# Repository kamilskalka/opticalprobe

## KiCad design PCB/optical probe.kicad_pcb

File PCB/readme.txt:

This folder contains the KiCad project and gerber files of the PCB

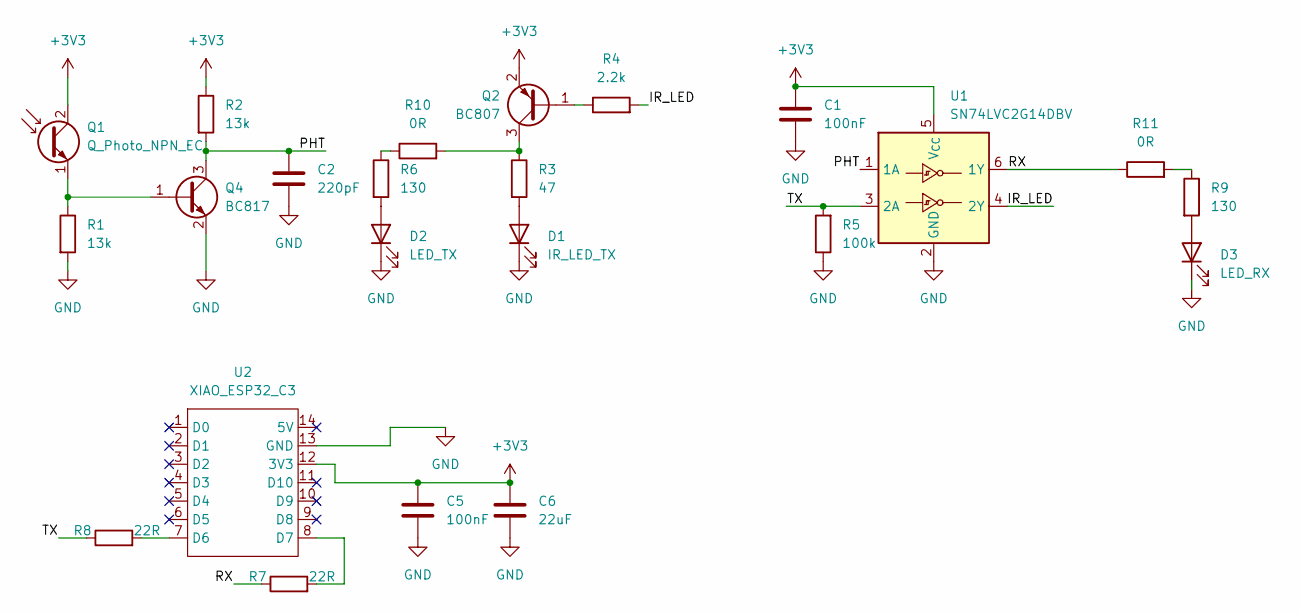
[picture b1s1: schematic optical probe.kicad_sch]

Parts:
C1, C5: 100nF; C_0805_2012Metric
C2: 220pF; C_0402_1005Metric_Pad0.74x0.62mm_HandSolder
C6: 22uF; C_1206_3216Metric
D1: IR_LED_TX; PT2651BTR8_reverse
D2: LED_TX; LED_0603_1608Metric
D3: LED_RX; LED_0603_1608Metric
Q1: Q_Photo_NPN_EC; PT2651BTR8_reverse
Q2: BC807; SOT-23
Q4: BC817; SOT-23
R1, R2: 13k; R_0402_1005Metric_Pad0.72x0.64mm_HandSolder
R3: 47; R_0402_1005Metric_Pad0.72x0.64mm_HandSolder
R4: 2.2k; R_0402_1005Metric_Pad0.72x0.64mm_HandSolder
R5: 100k; R_0402_1005Metric_Pad0.72x0.64mm_HandSolder
R6, R9: 130; R_0402_1005Metric_Pad0.72x0.64mm_HandSolder
R7, R8: 22R; R_0402_1005Metric_Pad0.72x0.64mm_HandSolder
R10, R11: 0R; R_0402_1005Metric_Pad0.72x0.64mm_HandSolder
U1: SN74LVC2G14DBV; SOT-23-6
U2: XIAO_ESP32_C3

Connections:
+3V3: C1.1, C5.1, C6.1, Q1.2 (C), Q2.2 (E), R2.1, U1.5 (V_{CC}), U2.12 (3V3)
/IR_LED: R4.2, U1.4 (2Y)
/PHT: C2.1, Q4.3 (C), R2.2, U1.1 (1A)
/RX: R7.1, R11.1, U1.6 (1Y)
/TX: R5.2, R8.1, U1.3 (2A)
GND: C1.2, C2.2, C5.2, C6.2, D1.1 (K), D2.1 (K), D3.1 (K), Q4.2 (E), R1.2, R5.1, U1.2 (GND), U2.13 (GND)
unnamed: D1.2 (A), R3.2
unnamed: D2.2 (A), R6.2
unnamed: D3.2 (A), R9.2
unnamed: Q1.1 (E), Q4.1 (B), R1.1
unnamed: Q2.1 (B), R4.1
unnamed: Q2.3 (C), R3.1, R10.2
unnamed: R6.1, R10.1
unnamed: R9.1, R11.2
unnamed: R8.2, U2.7 (D6)
unnamed: R7.2, U2.8 (D7)

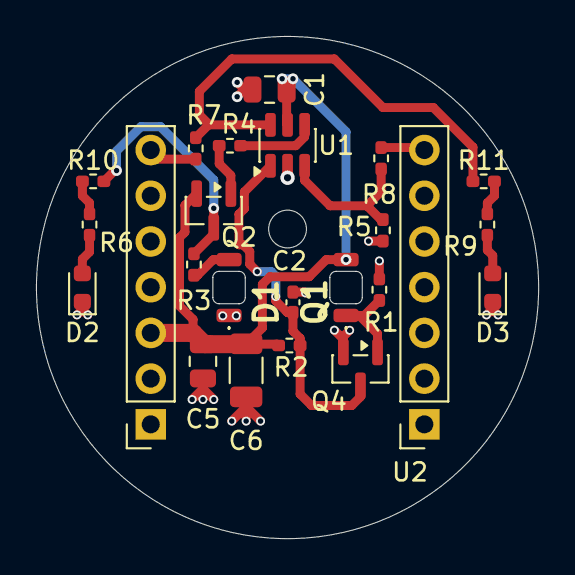
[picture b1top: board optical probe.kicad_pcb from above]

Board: 2 copper layers, 27.9 x 27.9 mm, 23 parts (0 on the bottom side), 16 nets.

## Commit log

2026-05-06 Create PCB
2026-05-09 Add files via upload
    Project documentation
